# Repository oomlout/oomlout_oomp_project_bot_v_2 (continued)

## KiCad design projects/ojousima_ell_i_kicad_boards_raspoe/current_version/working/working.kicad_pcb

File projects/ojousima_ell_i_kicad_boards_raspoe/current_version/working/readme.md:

# ell_i_kicad_boards
 
## summary 
* id: ojousima_ell_i_kicad_boards_raspoe
* user: ojousima
* name: ell_i_kicad_boards
* board: raspoe
* repo: https://github.com/ojousima/ELL-i-KiCAD-Boards
* src_file_repo_kicad_pcb: RasPoE/RasPoE.kicad_pcb
* src_file_repo_kicad_pcb_link: https://github.com/ojousima/ELL-i-KiCAD-Boards/tree/master/RasPoE/RasPoE.kicad_pcb

* src_file_repo_sch: RasPoE/RasPoE.sch
* src_file_repo_sch_link: https://github.com/ojousima/ELL-i-KiCAD-Boards/tree/master/RasPoE/RasPoE.sch
* full details link: https://github.com/oomlout/oomlout_oomp_project_bot_v_2/tree/main/projects/ojousima_ell_i_kicad_boards_raspoe/current_version/working

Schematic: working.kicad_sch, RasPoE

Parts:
B1, B2: MB110S; TO-269AA
C1, C2, C4, C5: 10n 100V; R_0603_HandSoldering
C3: 1n 2kV; C_1206_HandSoldering
C6: 470u; c_elec_10x10
C7, C8, C9: 4n7 2kV; C_1812_HandSoldering
C10: 100n; R_0603_HandSoldering
C11: 10u; R_0603_HandSoldering
D1: SMA58; Diode-SMA_Handsoldering
D2: LED; R_0603_HandSoldering
D3, D4: TVS; SOD-323
F1: PTC 1A25; R_1812
FB1, FB2, FB3, FB5, FB7, FB8: WE 742792651; R_0603_HandSoldering
FID1, FID2, FID3: 1, 2 mm; Fiducial_2mm_dia
J1: RJSSE-5080; RJSSE-5380
J2: RJSSE-5380
LOGO101: OPEN_HARDWARE_1; Symbol_OSHW-Logo_SilkScreen
LOGO102: ELL-i; ELL-i_large
P1: CONN_02X20; Pin_Header_Straight_2x20
P2: Screw terminal 2.54mm; Pin_Header_Straight_1x02
P101, P102: Wire pad; Pin_Header_Straight_1x01
R1, R2, R3, R4: 75R; R_0603_HandSoldering
R5: 180R; R_0603_HandSoldering
R6, R7: 100R 250 mW; R_0603_HandSoldering
R8, R9: R; R_0603_HandSoldering
TR1: WE_749012011
U1: AG9805-MT; AG9800

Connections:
+5V: F1.2, P1.2, P1.4
/ADJ: R8.2, R9.1, U1.4 (ADJ)
/AG_IN_+: C7.1, D1.1, FB7.2, P101.1, U1.5 (VIN+), U1.6 (VIN+)
/AG_IN_-: C8.1, D1.2, FB8.2, P102.1, U1.7 (VIN-), U1.8 (VIN-)
/AG_OUT_+: C6.1, C10.1, C11.1, F1.1, P2.1, R5.1, R6.1, R7.1, R8.1, U1.1 (VOUT+), U1.2 (VOUT+)
/POE_A+: B1.4, C4.1, TR1.2
/POE_A-: B1.2, C5.1, TR1.5
/POE_B+: B2.2, C2.1, J2.7, J2.8
/POE_B-: B2.4, C1.1, J2.4, J2.5
/RD+: D3.2, J1.3, TR1.10
/RD-: D3.1, J1.6, TR1.12
/RX+: J2.3, TR1.3
/RX-: J2.6, TR1.1
/TD+: D4.2, J1.1, TR1.7
/TD-: D4.1, J1.2, TR1.9
/TX+: J2.1, TR1.6
/TX-: J2.2, TR1.4
/VIN: B1.3 (+), B2.3 (+), FB1.1
GND: C6.2, C9.1, C10.2, C11.2, D2.1, P1.6, P1.9, P1.14, P1.20, P1.25, P1.30, P1.34, P1.39, P2.2, R6.2, R7.2, R9.2, U1.3 (VOUT-)
GNDA: C3.2, J2.9
GNDD: B1.1 (-), B2.1 (-), FB2.1
unnamed: C1.2, R1.1
unnamed: C2.2, R2.1
unnamed: C3.1, R1.2, R2.2, R3.2, R4.2
unnamed: C4.2, R3.1
unnamed: C5.2, R4.1
unnamed: C7.2, C8.2, C9.2
unnamed: D2.2, R5.2
unnamed: FB1.2, FB3.1
unnamed: FB2.2, FB5.1
unnamed: FB3.2, FB7.1
unnamed: FB5.2, FB8.1

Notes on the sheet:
Fiducials
ISOLATION 1.5kV Nominal
Less voltage
Raw PoE +
More voltage
Optional loading resistors
Raspberry Pi + Header
Raw PoE -
Unfused power to external devices
Logos

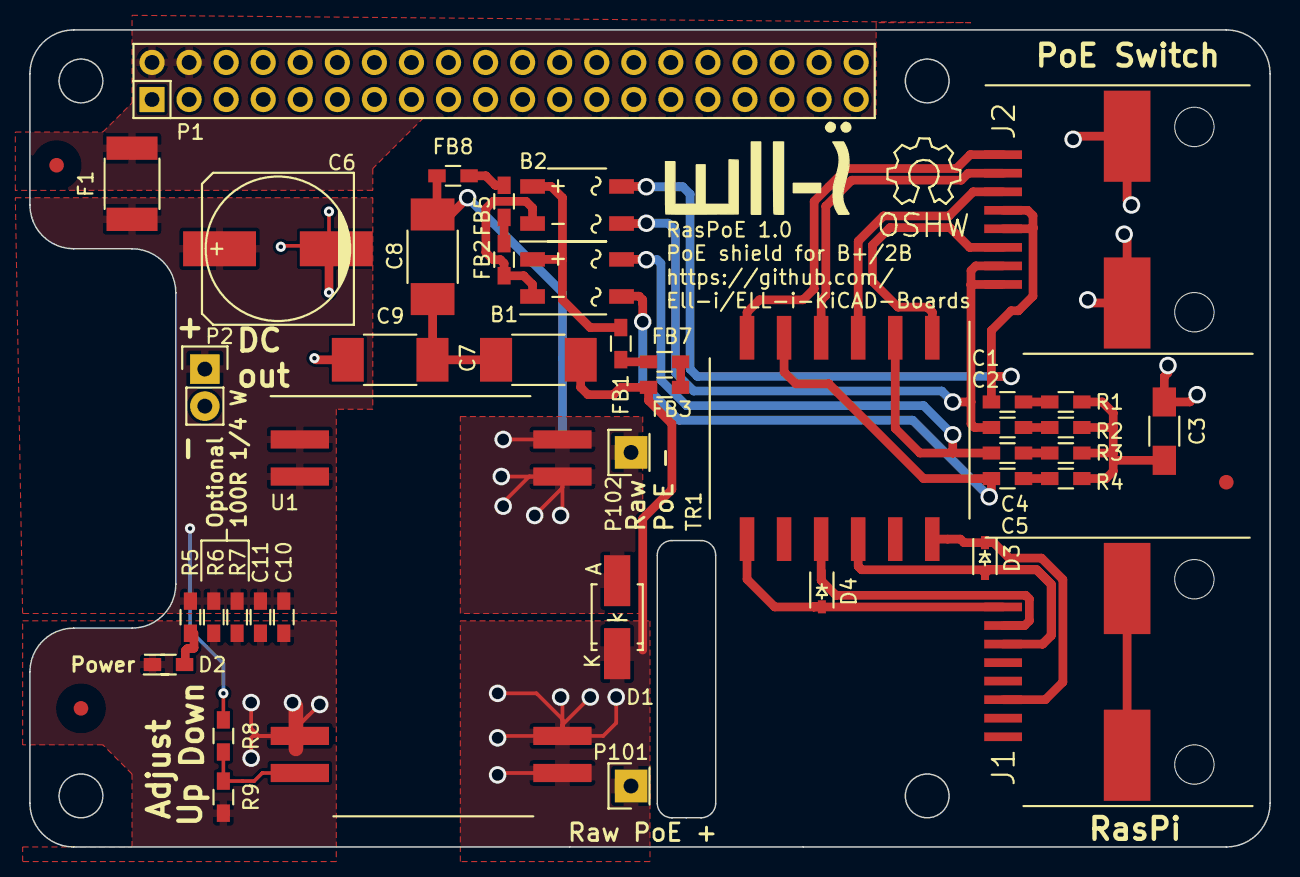
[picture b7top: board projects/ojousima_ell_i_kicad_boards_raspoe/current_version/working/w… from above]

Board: 2 copper layers, 85.0 x 56.0 mm, 46 parts (0 on the bottom side), 32 nets.

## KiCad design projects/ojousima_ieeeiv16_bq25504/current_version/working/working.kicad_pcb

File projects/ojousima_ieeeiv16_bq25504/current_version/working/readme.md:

# ieeeiv16
 
## summary 
* id: ojousima_ieeeiv16_bq25504
* user: ojousima
* name: ieeeiv16
* board: bq25504
* repo: https://github.com/ojousima/ieeeIV16
* src_file_repo_kicad_pcb: hardware/BQ25504/bq25504.kicad_pcb
* src_file_repo_kicad_pcb_link: https://github.com/ojousima/ieeeIV16/tree/master/hardware/BQ25504/bq25504.kicad_pcb

* src_file_repo_sch: hardware/BQ25504/bq25504.sch
* src_file_repo_sch_link: https://github.com/ojousima/ieeeIV16/tree/master/hardware/BQ25504/bq25504.sch
* full details link: https://github.com/oomlout/oomlout_oomp_project_bot_v_2/tree/main/projects/ojousima_ieeeiv16_bq25504/current_version/working

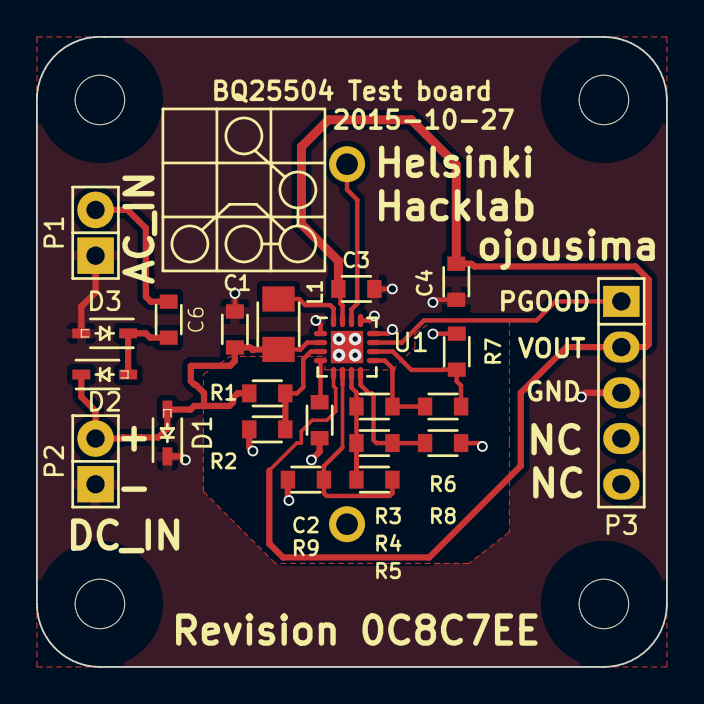
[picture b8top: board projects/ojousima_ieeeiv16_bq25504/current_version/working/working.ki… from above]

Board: 2 copper layers, 35.0 x 35.0 mm, 27 parts (1 on the bottom side), 15 nets.

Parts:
C1, C2, C3, C4, C6: C; SMD0603_A
C5: EECRG0V155(V|H)N; EECRG0V155HN
D1: TVS; SOD-323-A
D2, D3: D_Schottky; SOD-323-A
L1: INDUCTOR_SMALL; SMD1206_A
NC1, NC2, NC3, NC4: Mounting_hole; m2.5_mechanical_npth_mount
P1, P2: CONN_01X02; Pin_Header_Straight_1x02
P3: CONN_01X03; Pin_Header_Straight_1x05
R1, R2, R3, R4, R5, R6, R7, R8, R9: R_Small; SMD0603_A
U1: BQ25504; QFN-16-1EP_3x3mm_Pitch0.5mm

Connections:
/HYST: R3.2, R6.1, U1.9
/PROG: R6.2, R7.1, U1.10
/VBAT_OK: P3.1, U1.11
/VBOV: R5.2, R9.1, U1.6
/VBUV: R4.2, R8.1, U1.8
/V_IN: C1.1, D1.2, D2.1, L1.1, P2.2, R1.1, U1.2
/V_OC_SAMP: R1.2, R2.1, U1.3
/V_RDIV: R3.1, R4.1, R5.1, U1.7
/V_REF: C2.2, U1.4
/V_SYS: C3.1, C4.1, P3.2, U1.5, U1.15
GND: C1.2, C2.1, C3.2, C4.2, C5.2, D1.1, D3.2, P1.1, P2.1, P3.3, R2.2, R7.2, R8.2, R9.2, U1.1, U1.12, U1.13, U1.17
unnamed: C5.1, U1.14
unnamed: C6.1, D2.2, D3.1
unnamed: C6.2, P1.2
unnamed: L1.2, U1.16
